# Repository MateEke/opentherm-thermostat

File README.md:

# opentherm-thermostat

Project for esp32 based opentherm thermostat

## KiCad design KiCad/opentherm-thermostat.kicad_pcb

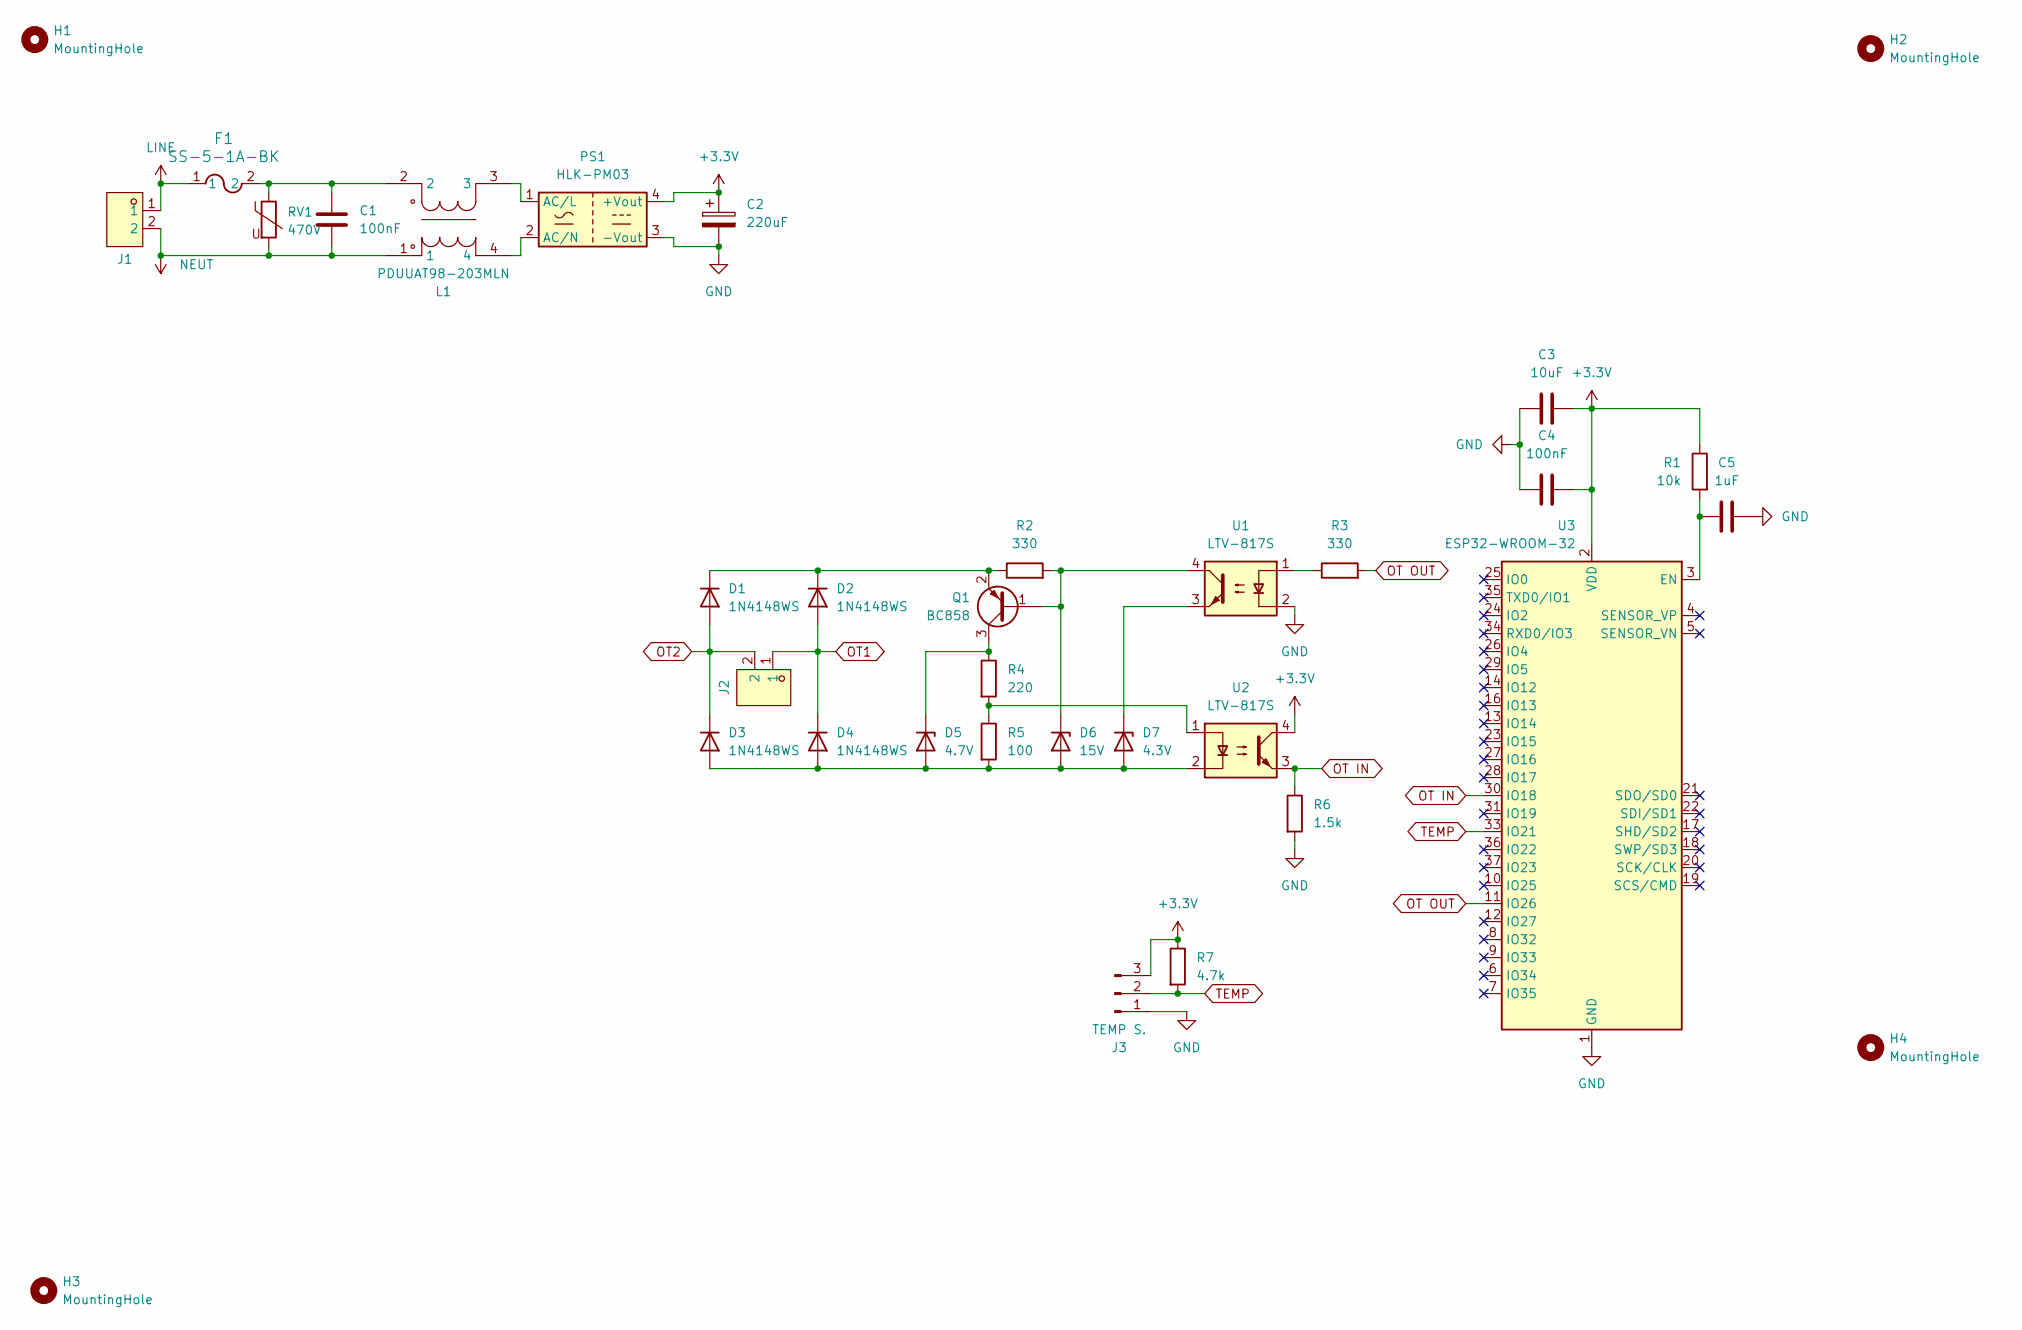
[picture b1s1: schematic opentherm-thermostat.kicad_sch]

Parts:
C1: 100nF; C_Rect_L18.0mm_W5.0mm_P15.00mm_FKS3_FKP3
C2: 220uF; CP_Radial_D6.3mm_P2.50mm
C3: 10uF; C_1206_3216Metric_Pad1.33x1.80mm_HandSolder
C4: 100nF; C_1206_3216Metric_Pad1.33x1.80mm_HandSolder
C5: 1uF; C_1206_3216Metric_Pad1.33x1.80mm_HandSolder
D1, D2, D3, D4: 1N4148WS; D_SOD-323_HandSoldering
D5: 4.7V; D_SOD-123F
D6: 15V; D_SOD-123F
D7: 4.3V; D_SOD-123F
F1: SS-5-1A-BK; FUS_CB_SS-5
H1, H2, H3, H4: MountingHole; MountingHole_3.2mm_M3_DIN965
J1, J2: KF301-5.0-2P; CONN-TH_P5.00_KF301-5.0-2P; LCSC Part C474881
J3: TEMP S.; JST_PH_S3B-PH-K_1x03_P2.00mm_Horizontal
L1: PDUUAT98-203MLN; FILTER-TH_4P-L17.0-W12.0-P7.00-D0.6-S8.00-1; LCSC Part C2923574
PS1: HLK-PM03; Converter_ACDC_Hi-Link_HLK-PMxx
Q1: BC858; SOT-23_Handsoldering
R1: 10k; R_1206_3216Metric_Pad1.30x1.75mm_HandSolder
R2, R3: 330; R_1206_3216Metric_Pad1.30x1.75mm_HandSolder
R4: 220; R_1206_3216Metric_Pad1.30x1.75mm_HandSolder
R5: 100; R_1206_3216Metric_Pad1.30x1.75mm_HandSolder
R6: 1.5k; R_1206_3216Metric_Pad1.30x1.75mm_HandSolder
R7: 4.7k; R_1206_3216Metric_Pad1.30x1.75mm_HandSolder
RV1: 470V; RV_Disc_D16.5mm_W6.7mm_P7.5mm
U1, U2: LTV-817S; SMDIP-4_W9.53mm
U3: ESP32-WROOM-32

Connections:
+3.3V: C2.1, C3.1, C4.1, J3.3, PS1.4 (+Vout), R1.1, R7.1, U2.4, U3.2 (VDD)
GND: C2.2, C3.2, C4.2, C5.1, J3.1, PS1.3 (-Vout), R6.2, U1.2, U3.1 (GND), U3.15 (GND), U3.38 (GND), U3.39 (GND)
LINE: F1.1, J1.1
NEUT: C1.2, J1.2, L1.1, RV1.2
unnamed: C1.1, F1.2, L1.2, RV1.1
unnamed: D1.1 (K), D2.1 (K), Q1.2 (E), R2.1
unnamed: D3.2 (A), D4.2 (A), D5.2 (A), D6.2 (A), D7.2 (A), R5.2, U2.2
unnamed: D5.1 (K), Q1.3 (C), R4.1
unnamed: D6.1 (K), Q1.1 (B), R2.2, U1.4
unnamed: D7.1 (K), U1.3
unnamed: L1.3, PS1.1 (AC/L)
unnamed: L1.4, PS1.2 (AC/N)
unnamed: R3.1, U1.1
unnamed: R4.2, R5.1, U2.1
unnamed: C5.2, R1.2, U3.3 (EN)
OT1: D2.2 (A), D4.1 (K), J2.1
OT2: D1.2 (A), D3.1 (K), J2.2
OT IN: R6.1, U2.3, U3.30 (IO18)
OT OUT: R3.2, U3.11 (IO26)
TEMP: J3.2, R7.2, U3.33 (IO21)

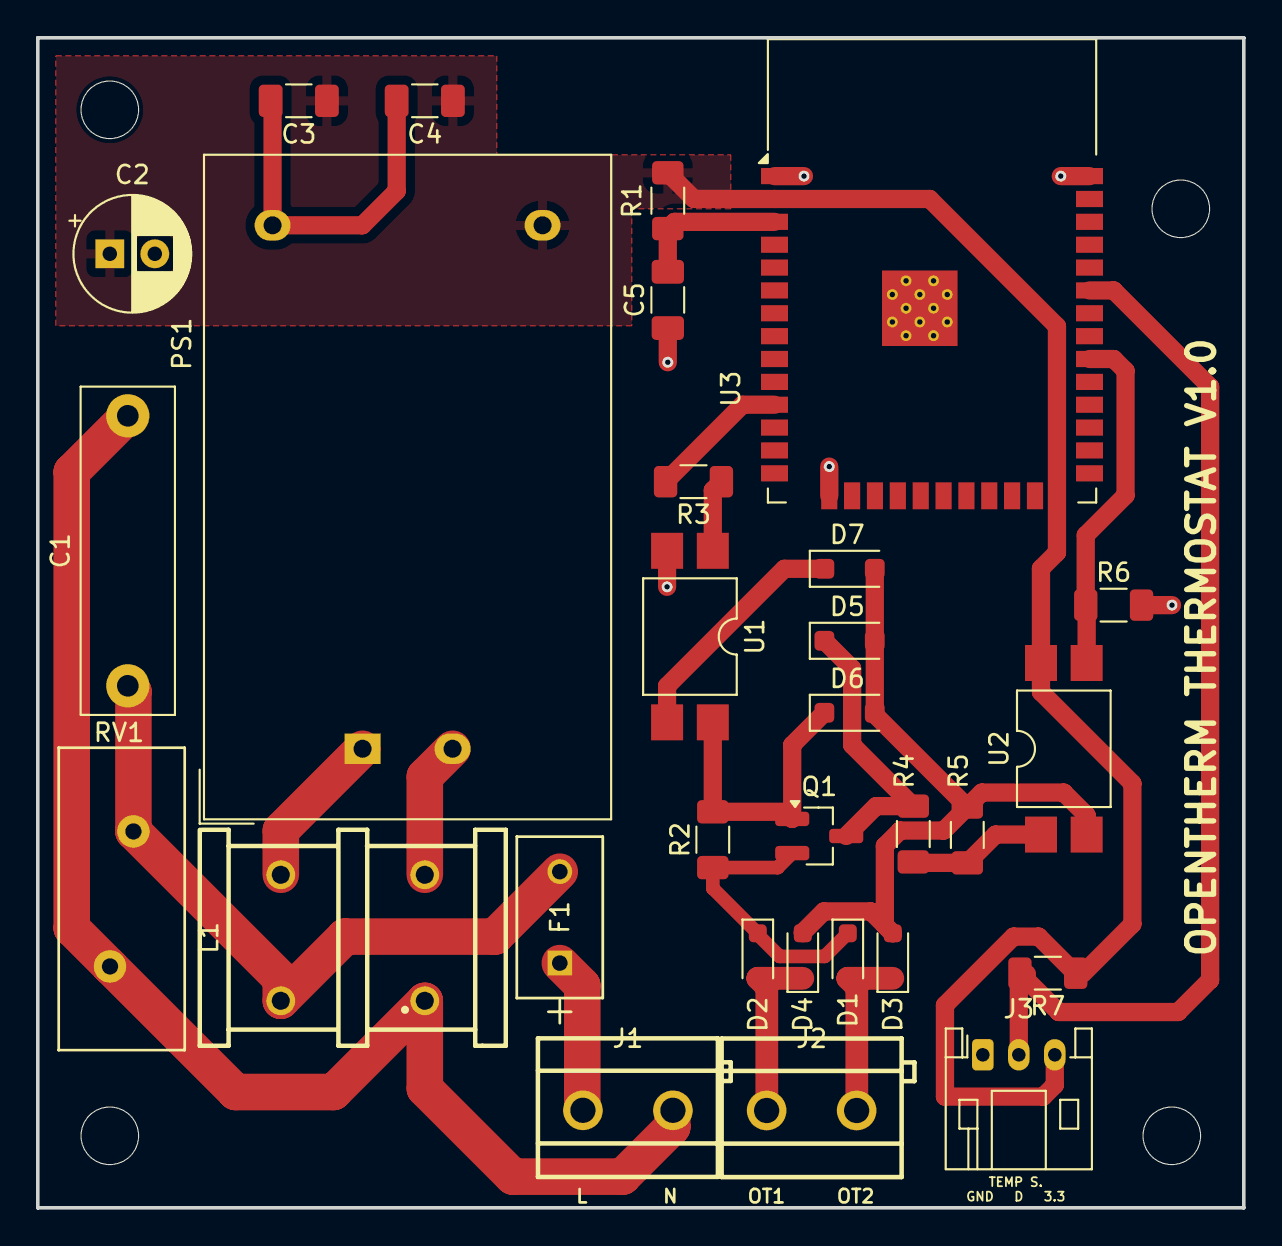
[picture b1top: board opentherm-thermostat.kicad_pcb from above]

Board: 2 copper layers, 67.0 x 65.0 mm, 34 parts (0 on the bottom side), 20 nets.

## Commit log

2024-12-13 initial pcb design
2024-12-13 add kicad library as submodule
2024-12-13 set up project specific libraries
2024-12-13 add esphome config
2024-12-14 init openscad model
2024-12-15 first version of the case
2024-12-18 v1 finished
2024-12-18 simplify scad
